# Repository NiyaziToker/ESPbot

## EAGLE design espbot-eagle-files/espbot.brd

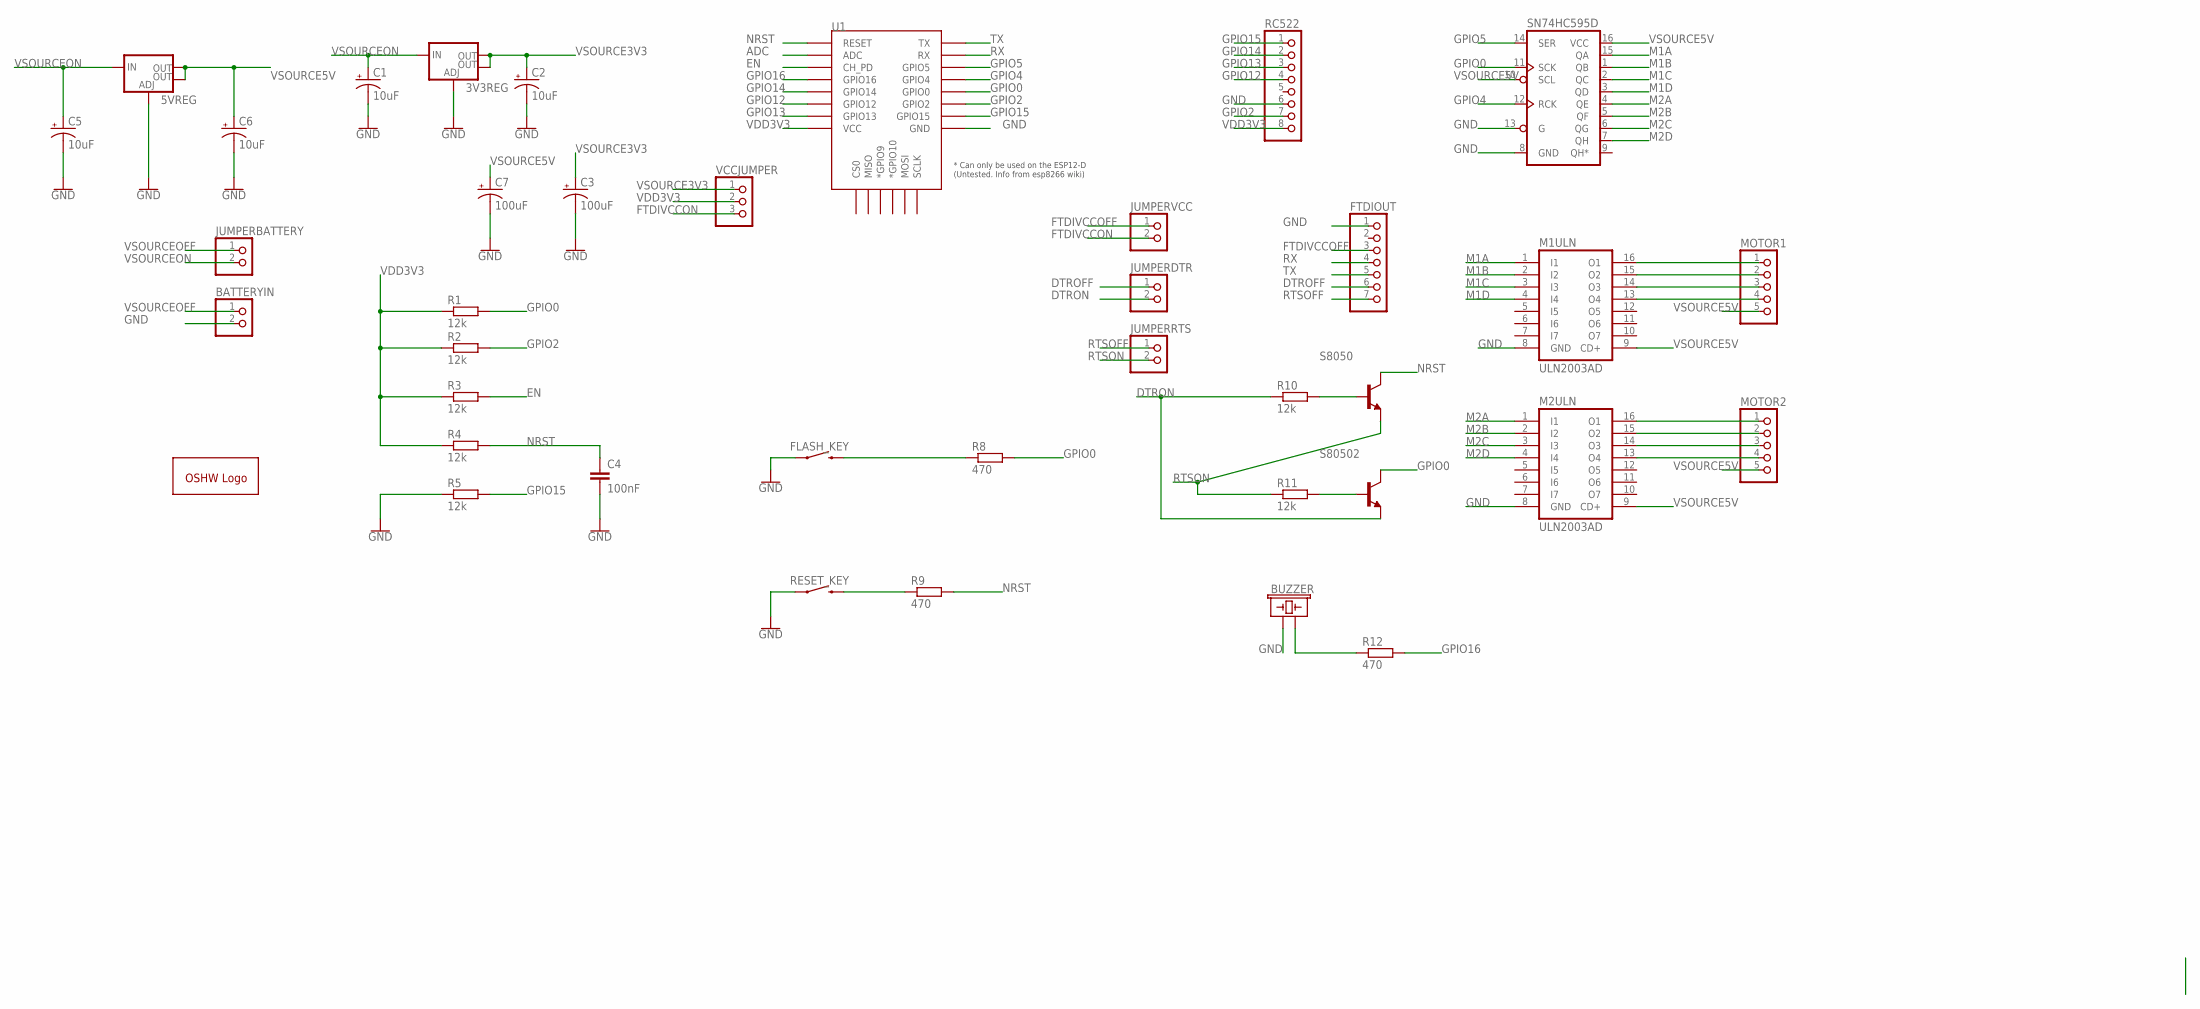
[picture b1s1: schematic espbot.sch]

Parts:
3V3REG, 5VREG: V_REG_LM1117SOT223; SOT223
BATTERYIN: PINHD-1X2; 1X02
BUZZER: BUZZER-PTH; BUZZER-12MM
C1, C2, C5, C6: 10uF; EIA3528
C3, C7: 100uF; EIA7343
C4: 100nF; C0805
FLASH_KEY: MOMENTARY-SWITCH-SPST-PTH-6.0MM; TACTILE_SWITCH_PTH_6.0MM
FTDIOUT: PINHD-1X7; 1X07
GOLD_ORB_SM1: OSHWLOGOLOGO5MM; OSHW_5MM
JUMPERBATTERY: PINHD-1X2; 1X02
JUMPERDTR: PINHD-1X2; 1X02
JUMPERRTS: PINHD-1X2; 1X02
JUMPERVCC: PINHD-1X2; 1X02
M1ULN, M2ULN: ULN2003AD; SO16
MOTOR1, MOTOR2: PINHD-1X5; 1X05
R1, R2, R3, R4, R5, R10, R11: 12k; R0805
R8, R9, R12: 470; R0805
RC522: PINHD-1X8; 1X08
RESET_KEY: MOMENTARY-SWITCH-SPST-PTH-6.0MM; TACTILE_SWITCH_PTH_6.0MM
S8050, S80502: 92-NPN-TO92-EBC; TO92-EBC
SN74HC595D: 74HC595D; SO16
U1: ESP12ESMD; ESP12E-SMD
VCCJUMPER: PINHD-1X3; 1X03

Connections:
ADC: U1.ADC
DTROFF: FTDIOUT.6, JUMPERDTR.1
DTRON: JUMPERDTR.2, R10.1, S80502.E
EN: R3.2, U1.CH_PD
FTDIVCCOFF: FTDIOUT.3, JUMPERVCC.1
FTDIVCCON: JUMPERVCC.2, VCCJUMPER.3
GND: 3V3REG.1 (ADJ), 5VREG.1 (ADJ), BATTERYIN.2, BUZZER.+ (1), C1.C (-), C2.C (-), C3.C (-), C4.2, C5.C (-), C6.C (-), C7.C (-), FLASH_KEY.1, FTDIOUT.1, M1ULN.8 (GND), M2ULN.8 (GND), R5.1, RC522.6, RESET_KEY.1, SN74HC595D.8 (GND), SN74HC595D.13 (G), U1.GND
GPIO0: R1.2, R8.2, S80502.C, SN74HC595D.11 (SCK), U1.GPIO0
GPIO2: R2.2, RC522.7, U1.GPIO2
GPIO4: SN74HC595D.12 (RCK), U1.GPIO4
GPIO5: SN74HC595D.14 (SER), U1.GPIO5
GPIO12: RC522.4, U1.GPIO12
GPIO13: RC522.3, U1.GPIO13
GPIO14: RC522.2, U1.GPIO14
GPIO15: R5.2, RC522.1, U1.GPIO15
GPIO16: R12.2, U1.GPIO16
M1A: M1ULN.1 (I1), SN74HC595D.15 (QA)
M1B: M1ULN.2 (I2), SN74HC595D.1 (QB)
M1C: M1ULN.3 (I3), SN74HC595D.2 (QC)
M1D: M1ULN.4 (I4), SN74HC595D.3 (QD)
M2A: M2ULN.1 (I1), SN74HC595D.4 (QE)
M2B: M2ULN.2 (I2), SN74HC595D.5 (QF)
M2C: M2ULN.3 (I3), SN74HC595D.6 (QG)
M2D: M2ULN.4 (I4), SN74HC595D.7 (QH)
unnamed: FLASH_KEY.3 (2), R8.1
unnamed: R9.1, RESET_KEY.3 (2)
unnamed: R10.2, S8050.B
unnamed: R11.2, S80502.B
unnamed: BUZZER.- (2), R12.1
unnamed: M2ULN.15 (O2), MOTOR2.2
unnamed: M1ULN.16 (O1), MOTOR1.1
unnamed: M1ULN.15 (O2), MOTOR1.2
unnamed: M1ULN.14 (O3), MOTOR1.3
unnamed: M1ULN.13 (O4), MOTOR1.4
unnamed: M2ULN.16 (O1), MOTOR2.1
unnamed: M2ULN.14 (O3), MOTOR2.3
unnamed: M2ULN.13 (O4), MOTOR2.4
NRST: C4.1, R4.2, R9.2, S8050.C, U1.RESET
RTSOFF: FTDIOUT.7, JUMPERRTS.1
RTSON: JUMPERRTS.2, R11.1, S8050.E
RX: FTDIOUT.4, U1.RXD0 (RX)
TX: FTDIOUT.5, U1.TXD0 (TX)
VDD3V3: R1.1, R2.1, R3.1, R4.1, RC522.8, U1.VCC, VCCJUMPER.2
VSOURCE3V3: 3V3REG.2 (OUT), 3V3REG.4 (OUT), C2.A (+), C3.A (+), VCCJUMPER.1
VSOURCE5V: 5VREG.2 (OUT), 5VREG.4 (OUT), C6.A (+), C7.A (+), M1ULN.9 (CD+), M2ULN.9 (CD+), MOTOR1.5, MOTOR2.5, SN74HC595D.10 (SCL), SN74HC595D.16 (VCC)
VSOURCEOFF: BATTERYIN.1, JUMPERBATTERY.1
VSOURCEON: 3V3REG.3 (IN), 5VREG.3 (IN), C1.A (+), C5.A (+), JUMPERBATTERY.2

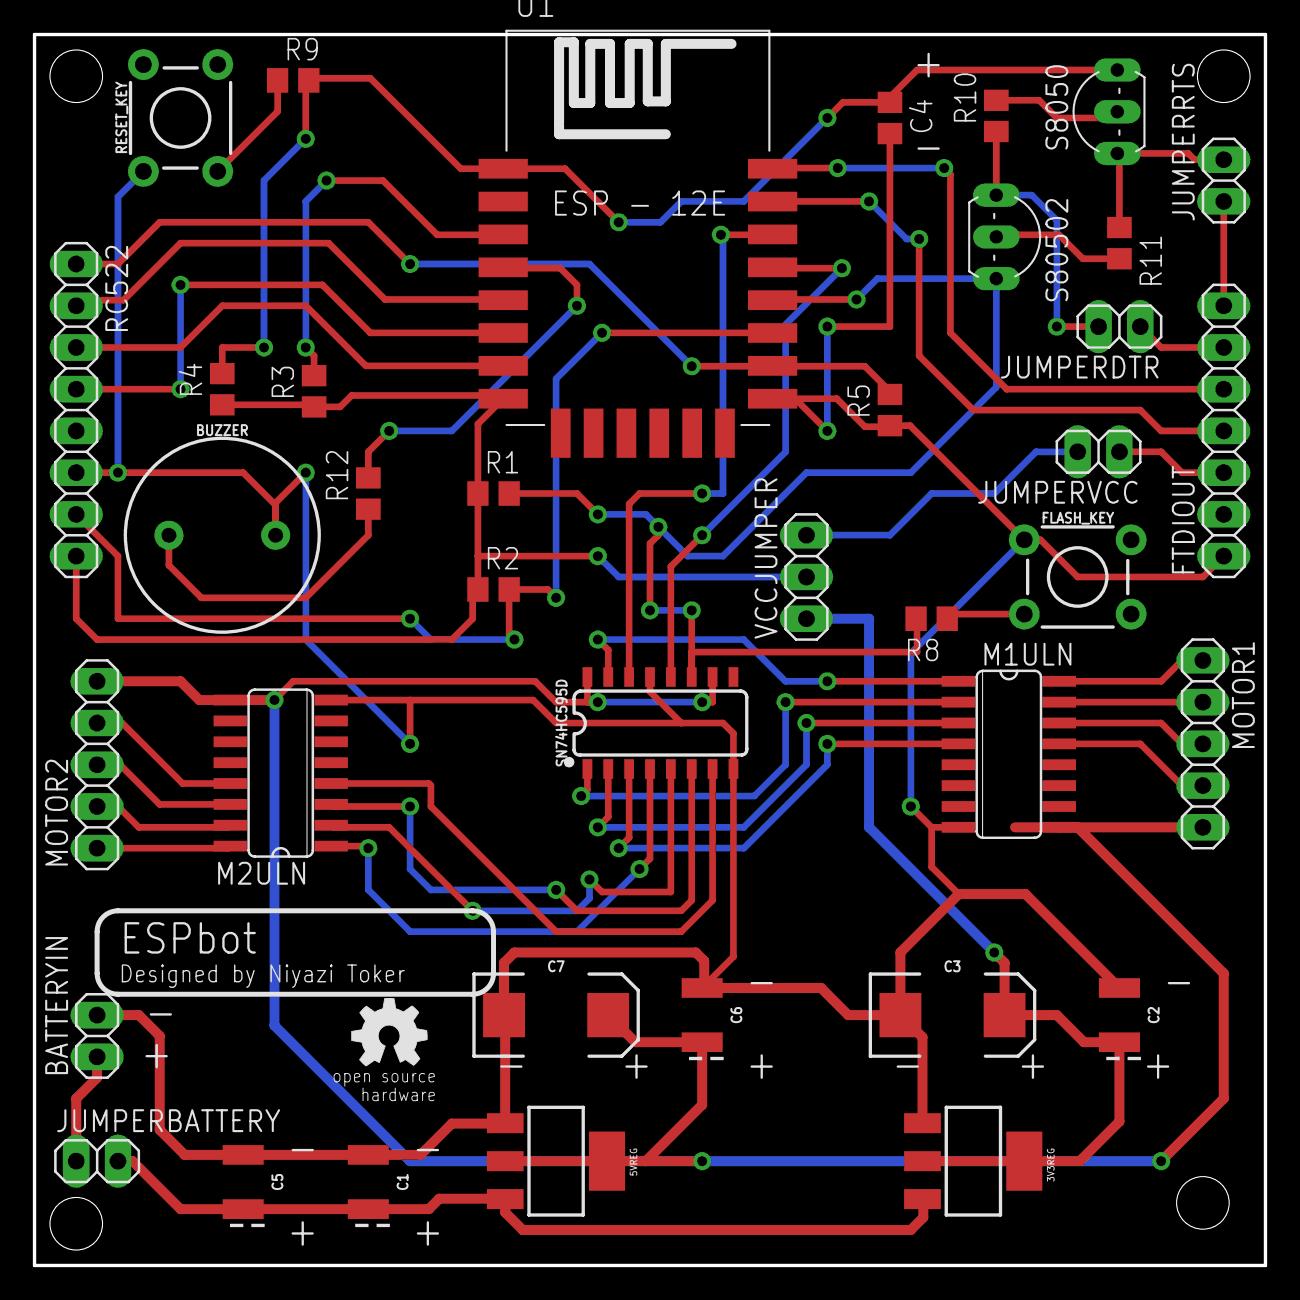
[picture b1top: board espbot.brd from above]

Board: 2 copper layers, 74.9 x 74.9 mm, 39 parts (0 on the bottom side), 46 nets.

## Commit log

2018-02-15 Added

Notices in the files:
parts and their libraries:
SparkFun-IC-Power: Licensing: Creative Commons ShareAlike 4.0 International - https://creativecommons.org/licenses/by-sa/4.0
